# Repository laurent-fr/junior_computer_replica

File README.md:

# Junior Computer Replica

The Junior Computer is a 6502 SBC made by Elektor in 1980. It looks a lot like a KIM-1.

This is a replica PCB I made with KiCAD.

The best source of information for this computer is Elektor Magazine from 80's , but you can find a lot on this website : http://retro.hansotten.nl/6502-sbc/elektuur-junior/

This board is not a 100% accurate replica, because I have added directly on the PCB a few updates published later by Elektor :
* a fix for memory decoding needed for the expansion board
* the main decoupling capacitor C2 was on wrong side of S25 (activate display) which could reset the computer
* a simple reset circuit with a resistor and a capacitor

I also replaced the 2708 EPROM by a 2716, which avoid the need of an hard to find EPROM & EPROM programmer, and has the big benefit of reducing the required power supplies from 3 (+5,-5,+12) to only +5V.

This work is licenced under CC BY-NC-SA (Attribution-NonCommercial-ShareAlike)

## BOM

| Qty | Reference   | Value | Comment |
| --- | --- | --- | --- |
| 1	| C1 |	10p | |
| 1	| C2 |	47µ 6V tantale | |
| 2	| C3, C4 |	100n MKH
| 8	| C5...C9, C10, C11, C14 | 	1µ 16V tantale | |
| 1	| C12 |	470nF MKH | |
| 2	| D1, D3 |	1N4148 | |
| 1	| IC1 |	MC6502 | |
| 1	| IC10 |	74LS01 | |
| 1	| IC11 |	ULN2003 | |
| 1	| IC2 |	2716 | |
| 1	| IC3 |	MC6532 | probably the first part to look at ! |
| 2	| IC4 IC5 |	2114 | static RAM, search on Ebay |
| 2	| IC7 IC6 |	74LS145 | |
| 1	| IC8 |	NE556 | |
| 1	| IC9 |	74LS00 | |
| 1	| J2 |	DIN41612 32 A+C angled male| |
| 1	| J3 |	DIN41617-31 straight female | |
| 2	| R17 R19 |	2k2 | |
| 2	| R18 R20 |	68k | |
| 1 | R1 | 330K | |
| 6	| R2 R3 R4 R16 R14 R15 |	3k3 | |
| 2	| R22 R21 |	1k | |
| 1	| R23 |	820k | |
| 1	| R5 |	4k7 | |
| 1	| R6 |	330 | |
| 7	| R7 R8 R9 R10 R12 R13 R11 |	68 | |
| 21	| S1…S23 |	Digitast 12.7mm | 16 black, 4 red, 1 red with integrated LED, 2 blue, but see below |
| 1	| S24 | DPDT lever switch	| with soldering lugs |
| 1	| S25|	SPDT lever switch | with soldering lugs |
| 1	| X.Tal1 |	1Mhz | can be hard to find ! |
| 3	| Socket DIP-14	| | |
| 3	| Socket DIP-16	| | |
| 2	| Socket DIP-18	| | |
| 1	| Socket DIP-24	| | |
| 2	| Socket DIP-40	| | |
| 6 | Di1 ... Di6 | MAN4640A | 7 segment display |

IF you cannot find 2114 RAMs , you can try the small board on "board adapter" folder (warning : not tested !) which should allow to use a 6116 RAM instead and plugs into the 2114 sockets

The Digitast keys (https://www.digikey.com/catalog/en/partgroup/digitast-series/15959) are the most expensives parts of this project. You can also use square tactile switchs instead (but it's not as pretty !)

An other thing to consider is the marking : the black keys need white marking, which can be hard to do. So think of how you will do the marking before choosing the colors of the keys !

## Ordering the PCB

Use you favorite online PCB seller, and order 2 double-sided PCBs (display + computer) from the KiCad output files.

The real ones from Elektor where blue on component side and red on solder side, but if you order a blue PCB it will be close enough (and very nice).

## Building the computer

The building is pretty straightforward (look at the original documentation). Components are soldered on one side, buttons and disply on the other side.

S24 and S25 switchs needs wires from the switchs lugs to the PCB (I used cutoff of resistor leads)

To connect the display to the main board, I used long SIL connectors (15-20mm long) soldered on both side, then I bent the display to ~30°

Don't forget the two small wire jumpers on front side : one from ground to letter "D" and the other one from K6 to the center pin.

If you want to use the file sticker-juniorcomputer.svg, first install the font "Microgramma D Extended Bold" on your system.

## Programming the EPROM

I use a TL866 II plus for this, but anything that works is OK. 

Program the 2716 with the file 2716_junior_monitor_ram_05_1980.bin

## First tests

The power supply is available on both connectors, you just need 0v and +5V (1amp should be more than enough).

All the display should light up (check that the DISPLAY switch is ON). If you see some display ON, some display OFF, it could be a bad MC6532 (don't ask how I know that ...)

If nothing happens, press the reset switch to start the computer.

Typing numbers on keyboard should update the display.

You can find test programs on http://retro.hansotten.nl

## Going further

It would be great to be able to load and save data, and also to have a serial terminal for typing programs. It's exactly the purpose of the Junior Interface board ! Look into the folder "junior-interface" for more infos !

Now I'm sure you want to run BASIC on the Junior, no problem, just build the memory expansion from "junior-universal-memory" folder and you're good to go !

## Status

### Working

* junior-computer : the computer, built and tested OK
* junior-computer-display: the 7 segments display, built and tested OK
* junior-interface : the 2nd board adding various I/O to the computer, built and tested OK
* junior-internal-conn : internal bus between computer and interface, built and tested OK
* junior-internal-bus : a small PCB for linking the computer and the interface board, built and tested OK
* junior-bus : Elektor expansion bus. Not tested, built and tested OK
* junior-universal-memory : a RAM/EPROM board for the computer, built and tested OK

### Not tested

* ram-adapter : replace 2x2114 by 1x6116 RAM. Not tested

```
Any question ? --> Mastodon @LaurentFr@piaille.fr
```

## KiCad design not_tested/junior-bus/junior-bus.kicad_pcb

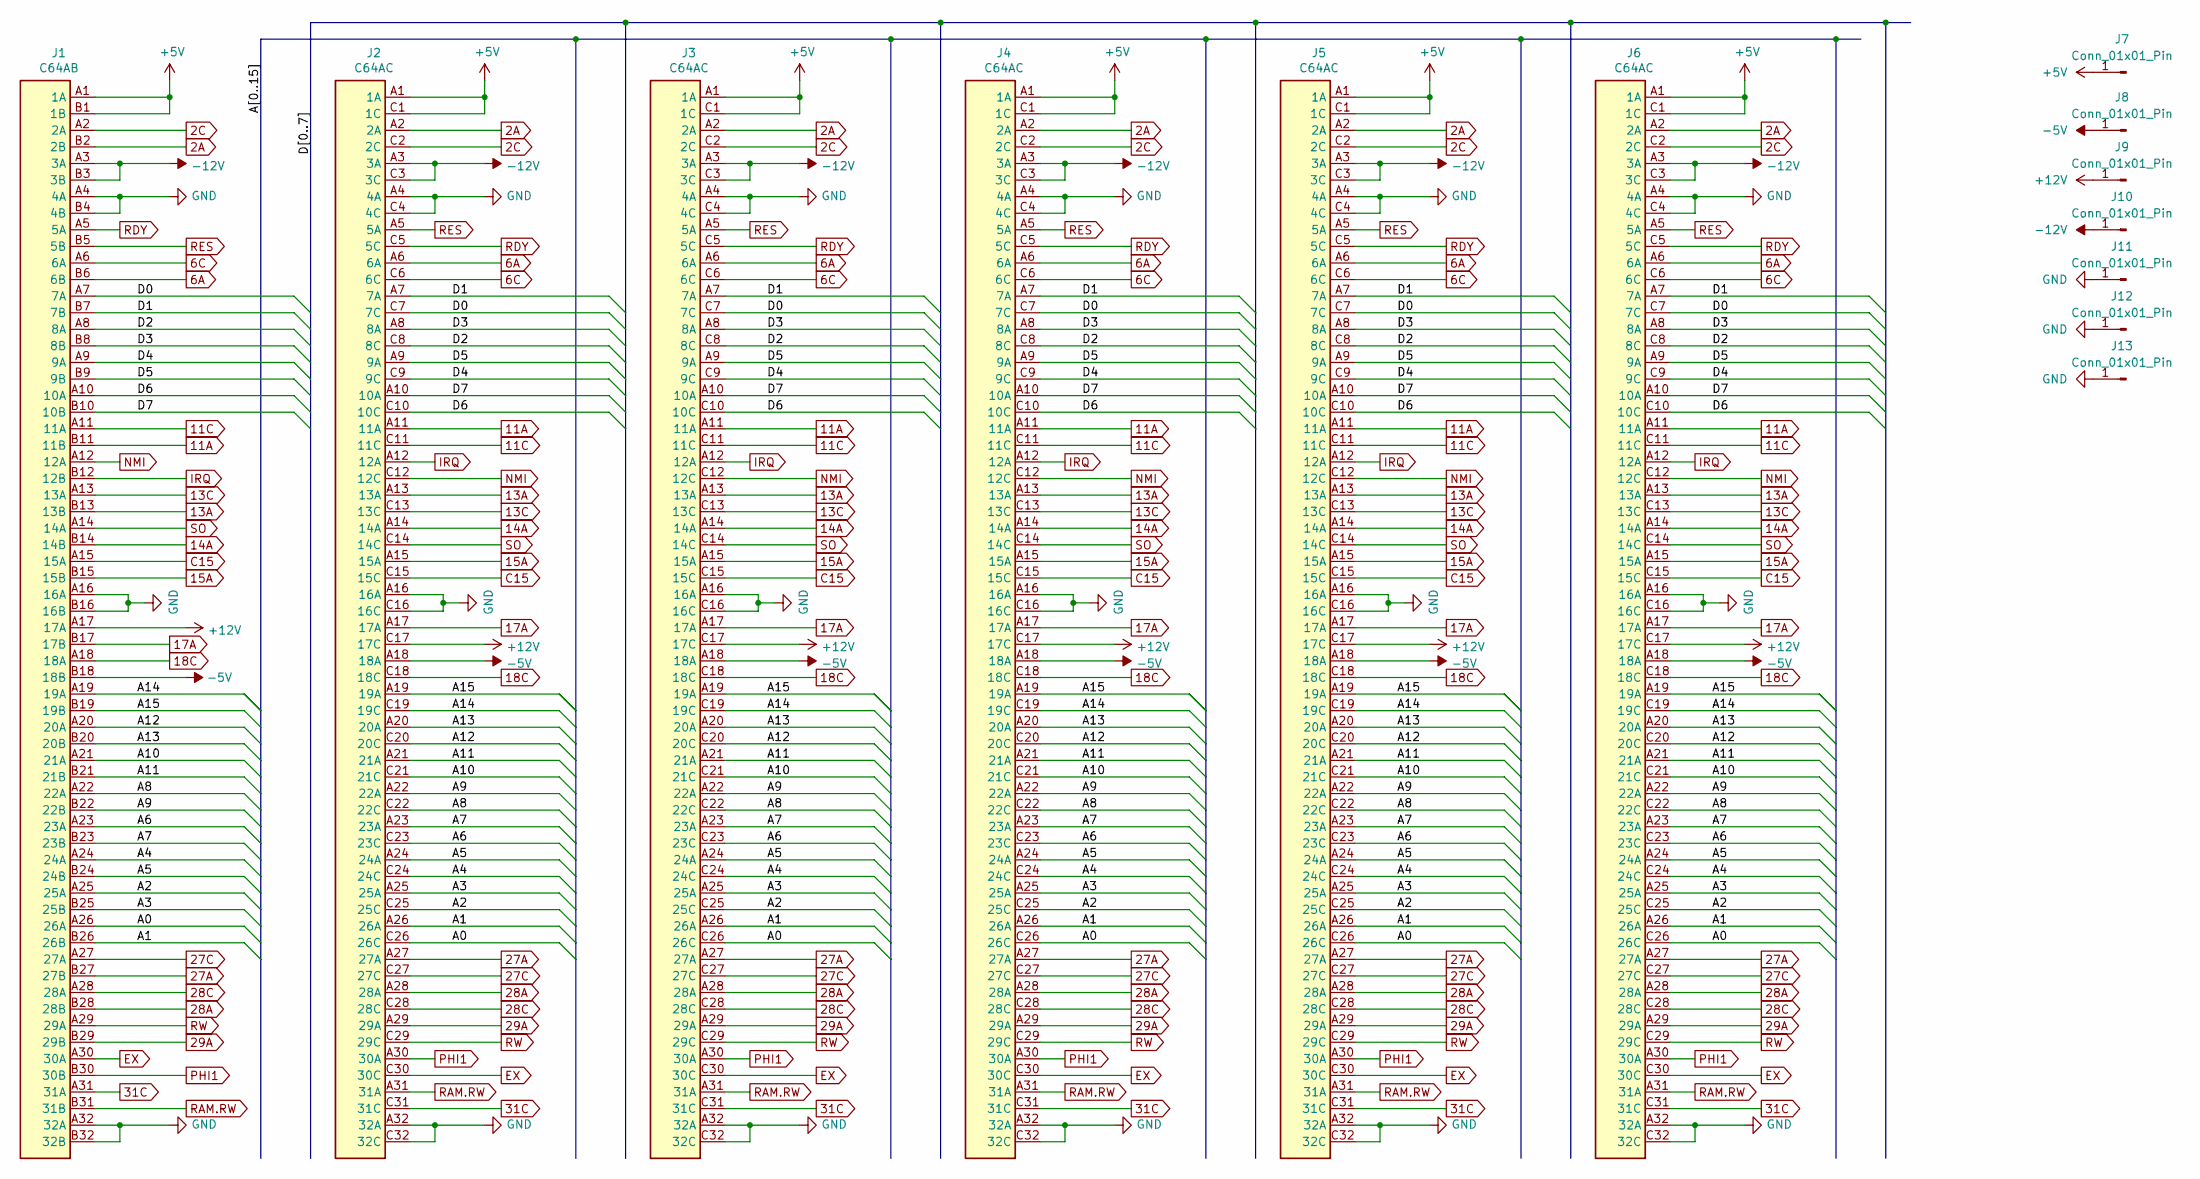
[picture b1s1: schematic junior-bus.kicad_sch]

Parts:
J1: C64AB; DIN-41612-AB-small-pads
J2, J3, J4, J5, J6: C64AC; DI41612-AC-F
J7, J8, J9, J10, J11, J12, J13: Conn_01x01_Pin; PIN

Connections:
2A: J1.B2 (2B), J2.A2 (2A), J3.A2 (2A), J4.A2 (2A), J5.A2 (2A), J6.A2 (2A)
2C: J1.A2 (2A), J2.C2 (2C), J3.C2 (2C), J4.C2 (2C), J5.C2 (2C), J6.C2 (2C)
6A: J1.B6 (6B), J2.A6 (6A), J3.A6 (6A), J4.A6 (6A), J5.A6 (6A), J6.A6 (6A)
6C: J1.A6 (6A), J2.C6 (6C), J3.C6 (6C), J4.C6 (6C), J5.C6 (6C), J6.C6 (6C)
11A: J1.B11 (11B), J2.A11 (11A), J3.A11 (11A), J4.A11 (11A), J5.A11 (11A), J6.A11 (11A)
11C: J1.A11 (11A), J2.C11 (11C), J3.C11 (11C), J4.C11 (11C), J5.C11 (11C), J6.C11 (11C)
13A: J1.B13 (13B), J2.A13 (13A), J3.A13 (13A), J4.A13 (13A), J5.A13 (13A), J6.A13 (13A)
13C: J1.A13 (13A), J2.C13 (13C), J3.C13 (13C), J4.C13 (13C), J5.C13 (13C), J6.C13 (13C)
14A: J1.B14 (14B), J2.A14 (14A), J3.A14 (14A), J4.A14 (14A), J5.A14 (14A), J6.A14 (14A)
15A: J1.B15 (15B), J2.A15 (15A), J3.A15 (15A), J4.A15 (15A), J5.A15 (15A), J6.A15 (15A)
17A: J1.B17 (17B), J2.A17 (17A), J3.A17 (17A), J4.A17 (17A), J5.A17 (17A), J6.A17 (17A)
18C: J1.A18 (18A), J2.C18 (18C), J3.C18 (18C), J4.C18 (18C), J5.C18 (18C), J6.C18 (18C)
27A: J1.B27 (27B), J2.A27 (27A), J3.A27 (27A), J4.A27 (27A), J5.A27 (27A), J6.A27 (27A)
27C: J1.A27 (27A), J2.C27 (27C), J3.C27 (27C), J4.C27 (27C), J5.C27 (27C), J6.C27 (27C)
28A: J1.B28 (28B), J2.A28 (28A), J3.A28 (28A), J4.A28 (28A), J5.A28 (28A), J6.A28 (28A)
28C: J1.A28 (28A), J2.C28 (28C), J3.C28 (28C), J4.C28 (28C), J5.C28 (28C), J6.C28 (28C)
29A: J1.B29 (29B), J2.A29 (29A), J3.A29 (29A), J4.A29 (29A), J5.A29 (29A), J6.A29 (29A)
31C: J1.A31 (31A), J2.C31 (31C), J3.C31 (31C), J4.C31 (31C), J5.C31 (31C), J6.C31 (31C)
+5V: J1.A1 (1A), J1.B1 (1B), J2.A1 (1A), J2.C1 (1C), J3.A1 (1A), J3.C1 (1C), J4.A1 (1A), J4.C1 (1C), J5.A1 (1A), J5.C1 (1C), J6.A1 (1A), J6.C1 (1C), J7.1
+12V: J1.A17 (17A), J2.C17 (17C), J3.C17 (17C), J4.C17 (17C), J5.C17 (17C), J6.C17 (17C), J9.1
-5V: J1.B18 (18B), J2.A18 (18A), J3.A18 (18A), J4.A18 (18A), J5.A18 (18A), J6.A18 (18A), J8.1
-12V: J1.A3 (3A), J1.B3 (3B), J2.A3 (3A), J2.C3 (3C), J3.A3 (3A), J3.C3 (3C), J4.A3 (3A), J4.C3 (3C), J5.A3 (3A), J5.C3 (3C), J6.A3 (3A), J6.C3 (3C), J10.1
/A0: J1.A26 (26A), J2.C26 (26C), J3.C26 (26C), J4.C26 (26C), J5.C26 (26C), J6.C26 (26C)
/A1: J1.B26 (26B), J2.A26 (26A), J3.A26 (26A), J4.A26 (26A), J5.A26 (26A), J6.A26 (26A)
/A2: J1.A25 (25A), J2.C25 (25C), J3.C25 (25C), J4.C25 (25C), J5.C25 (25C), J6.C25 (25C)
/A3: J1.B25 (25B), J2.A25 (25A), J3.A25 (25A), J4.A25 (25A), J5.A25 (25A), J6.A25 (25A)
/A4: J1.A24 (24A), J2.C24 (24C), J3.C24 (24C), J4.C24 (24C), J5.C24 (24C), J6.C24 (24C)
/A5: J1.B24 (24B), J2.A24 (24A), J3.A24 (24A), J4.A24 (24A), J5.A24 (24A), J6.A24 (24A)
/A6: J1.A23 (23A), J2.C23 (23C), J3.C23 (23C), J4.C23 (23C), J5.C23 (23C), J6.C23 (23C)
/A7: J1.B23 (23B), J2.A23 (23A), J3.A23 (23A), J4.A23 (23A), J5.A23 (23A), J6.A23 (23A)
/A8: J1.A22 (22A), J2.C22 (22C), J3.C22 (22C), J4.C22 (22C), J5.C22 (22C), J6.C22 (22C)
/A9: J1.B22 (22B), J2.A22 (22A), J3.A22 (22A), J4.A22 (22A), J5.A22 (22A), J6.A22 (22A)
/A10: J1.A21 (21A), J2.C21 (21C), J3.C21 (21C), J4.C21 (21C), J5.C21 (21C), J6.C21 (21C)
/A11: J1.B21 (21B), J2.A21 (21A), J3.A21 (21A), J4.A21 (21A), J5.A21 (21A), J6.A21 (21A)
/A12: J1.A20 (20A), J2.C20 (20C), J3.C20 (20C), J4.C20 (20C), J5.C20 (20C), J6.C20 (20C)
/A13: J1.B20 (20B), J2.A20 (20A), J3.A20 (20A), J4.A20 (20A), J5.A20 (20A), J6.A20 (20A)
/A14: J1.A19 (19A), J2.C19 (19C), J3.C19 (19C), J4.C19 (19C), J5.C19 (19C), J6.C19 (19C)
/A15: J1.B19 (19B), J2.A19 (19A), J3.A19 (19A), J4.A19 (19A), J5.A19 (19A), J6.A19 (19A)
/D0: J1.A7 (7A), J2.C7 (7C), J3.C7 (7C), J4.C7 (7C), J5.C7 (7C), J6.C7 (7C)
/D1: J1.B7 (7B), J2.A7 (7A), J3.A7 (7A), J4.A7 (7A), J5.A7 (7A), J6.A7 (7A)
/D2: J1.A8 (8A), J2.C8 (8C), J3.C8 (8C), J4.C8 (8C), J5.C8 (8C), J6.C8 (8C)
/D3: J1.B8 (8B), J2.A8 (8A), J3.A8 (8A), J4.A8 (8A), J5.A8 (8A), J6.A8 (8A)
/D4: J1.A9 (9A), J2.C9 (9C), J3.C9 (9C), J4.C9 (9C), J5.C9 (9C), J6.C9 (9C)
/D5: J1.B9 (9B), J2.A9 (9A), J3.A9 (9A), J4.A9 (9A), J5.A9 (9A), J6.A9 (9A)
/D6: J1.A10 (10A), J2.C10 (10C), J3.C10 (10C), J4.C10 (10C), J5.C10 (10C), J6.C10 (10C)
/D7: J1.B10 (10B), J2.A10 (10A), J3.A10 (10A), J4.A10 (10A), J5.A10 (10A), J6.A10 (10A)
C15: J1.A15 (15A), J2.C15 (15C), J3.C15 (15C), J4.C15 (15C), J5.C15 (15C), J6.C15 (15C)
EX: J1.A30 (30A), J2.C30 (30C), J3.C30 (30C), J4.C30 (30C), J5.C30 (30C), J6.C30 (30C)
GND: J1.A4 (4A), J1.A16 (16A), J1.A32 (32A), J1.B4 (4B), J1.B16 (16B), J1.B32 (32B), J2.A4 (4A), J2.A16 (16A), J2.A32 (32A), J2.C4 (4C), J2.C16 (16C), J2.C32 (32C), J3.A4 (4A), J3.A16 (16A), J3.A32 (32A), J3.C4 (4C), J3.C16 (16C), J3.C32 (32C), J4.A4 (4A), J4.A16 (16A), J4.A32 (32A), J4.C4 (4C), J4.C16 (16C), J4.C32 (32C), J5.A4 (4A), J5.A16 (16A), J5.A32 (32A), J5.C4 (4C), J5.C16 (16C), J5.C32 (32C), J6.A4 (4A), J6.A16 (16A), J6.A32 (32A), J6.C4 (4C), J6.C16 (16C), J6.C32 (32C), J11.1, J12.1, J13.1
IRQ: J1.B12 (12B), J2.A12 (12A), J3.A12 (12A), J4.A12 (12A), J5.A12 (12A), J6.A12 (12A)
NMI: J1.A12 (12A), J2.C12 (12C), J3.C12 (12C), J4.C12 (12C), J5.C12 (12C), J6.C12 (12C)
PHI1: J1.B30 (30B), J2.A30 (30A), J3.A30 (30A), J4.A30 (30A), J5.A30 (30A), J6.A30 (30A)
RAM.RW: J1.B31 (31B), J2.A31 (31A), J3.A31 (31A), J4.A31 (31A), J5.A31 (31A), J6.A31 (31A)
RDY: J1.A5 (5A), J2.C5 (5C), J3.C5 (5C), J4.C5 (5C), J5.C5 (5C), J6.C5 (5C)
RES: J1.B5 (5B), J2.A5 (5A), J3.A5 (5A), J4.A5 (5A), J5.A5 (5A), J6.A5 (5A)
RW: J1.A29 (29A), J2.C29 (29C), J3.C29 (29C), J4.C29 (29C), J5.C29 (29C), J6.C29 (29C)
SO: J1.A14 (14A), J2.C14 (14C), J3.C14 (14C), J4.C14 (14C), J5.C14 (14C), J6.C14 (14C)

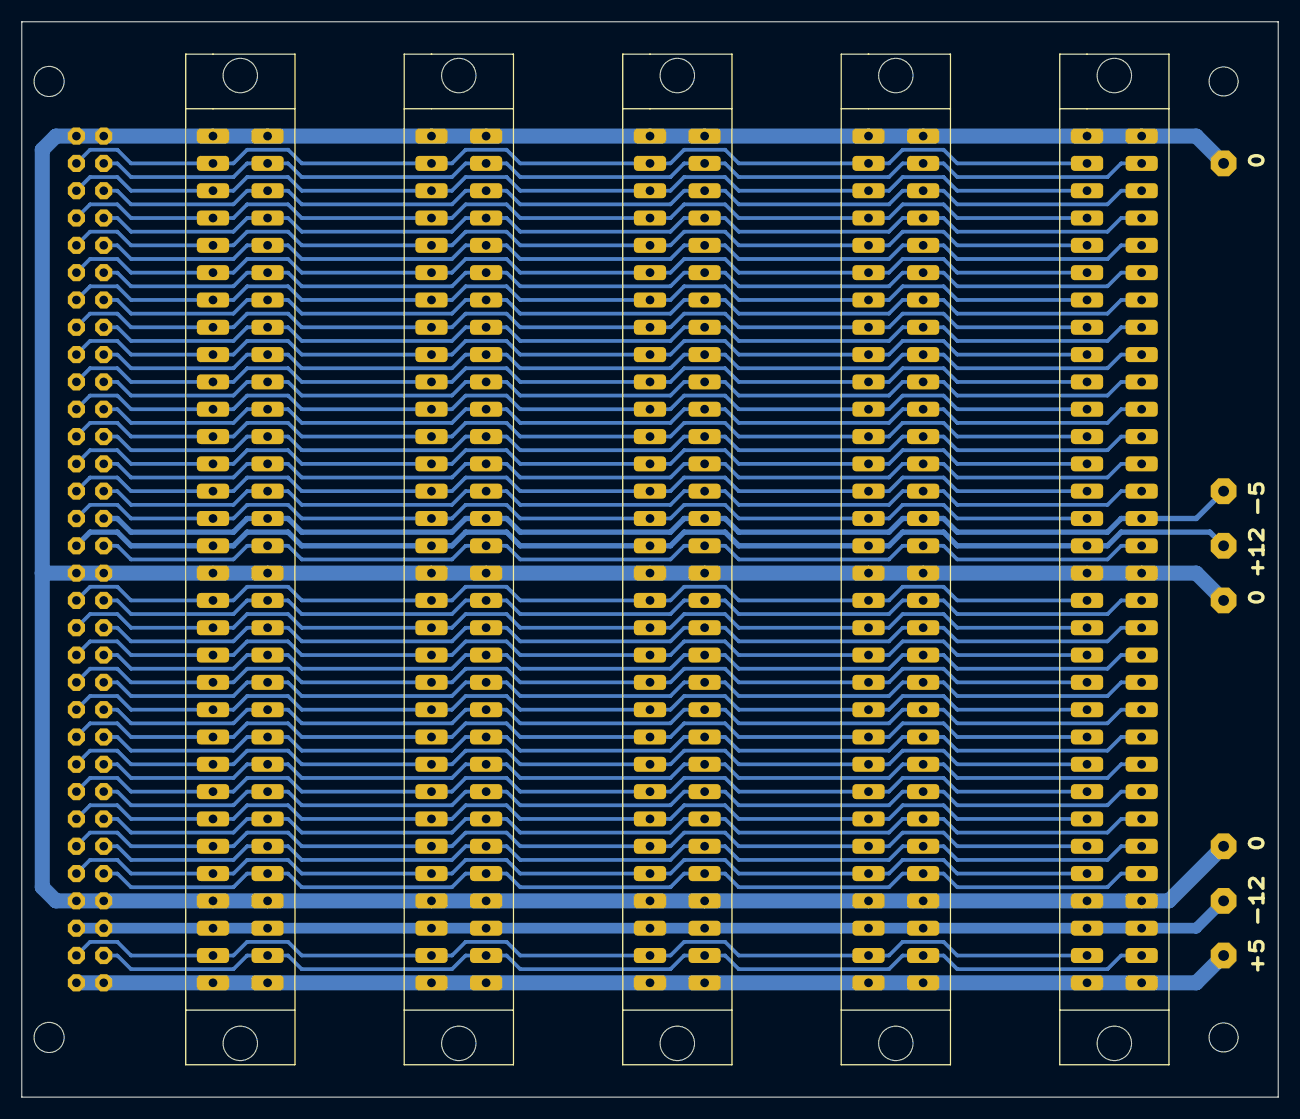
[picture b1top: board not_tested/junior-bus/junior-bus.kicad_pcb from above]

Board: 2 copper layers, 116.8 x 100.0 mm, 15 parts (1 on the bottom side), 57 nets.

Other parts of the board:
REF1, REF2: MountingHole_2.7mm_M2.5_ISO14580

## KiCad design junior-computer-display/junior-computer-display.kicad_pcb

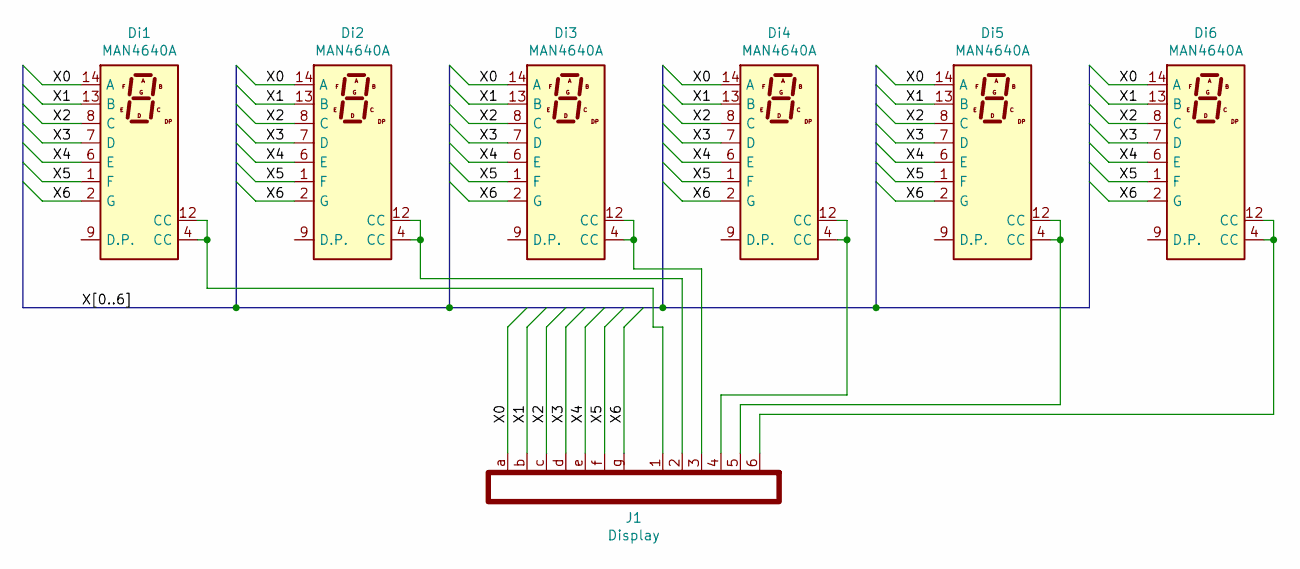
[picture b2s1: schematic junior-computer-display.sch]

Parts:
Di1, Di2, Di3, Di4, Di5, Di6: MAN4640A; 7SEGMENT
J1: Display; Conn-Display-Top

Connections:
/X0: Di1.14 (A), Di2.14 (A), Di3.14 (A), Di4.14 (A), Di5.14 (A), Di6.14 (A), J1.a
/X1: Di1.13 (B), Di2.13 (B), Di3.13 (B), Di4.13 (B), Di5.13 (B), Di6.13 (B), J1.b
/X2: Di1.8 (C), Di2.8 (C), Di3.8 (C), Di4.8 (C), Di5.8 (C), Di6.8 (C), J1.c
/X3: Di1.7 (D), Di2.7 (D), Di3.7 (D), Di4.7 (D), Di5.7 (D), Di6.7 (D), J1.d
/X4: Di1.6 (E), Di2.6 (E), Di3.6 (E), Di4.6 (E), Di5.6 (E), Di6.6 (E), J1.e
/X5: Di1.1 (F), Di2.1 (F), Di3.1 (F), Di4.1 (F), Di5.1 (F), Di6.1 (F), J1.f
/X6: Di1.2 (G), Di2.2 (G), Di3.2 (G), Di4.2 (G), Di5.2 (G), Di6.2 (G), J1.g
unnamed: Di1.4 (CC), Di1.12 (CC), J1.1
unnamed: Di2.4 (CC), Di2.12 (CC), J1.2
unnamed: Di3.4 (CC), Di3.12 (CC), J1.3
unnamed: Di4.4 (CC), Di4.12 (CC), J1.4
unnamed: Di5.4 (CC), Di5.12 (CC), J1.5
unnamed: Di6.4 (CC), Di6.12 (CC), J1.6

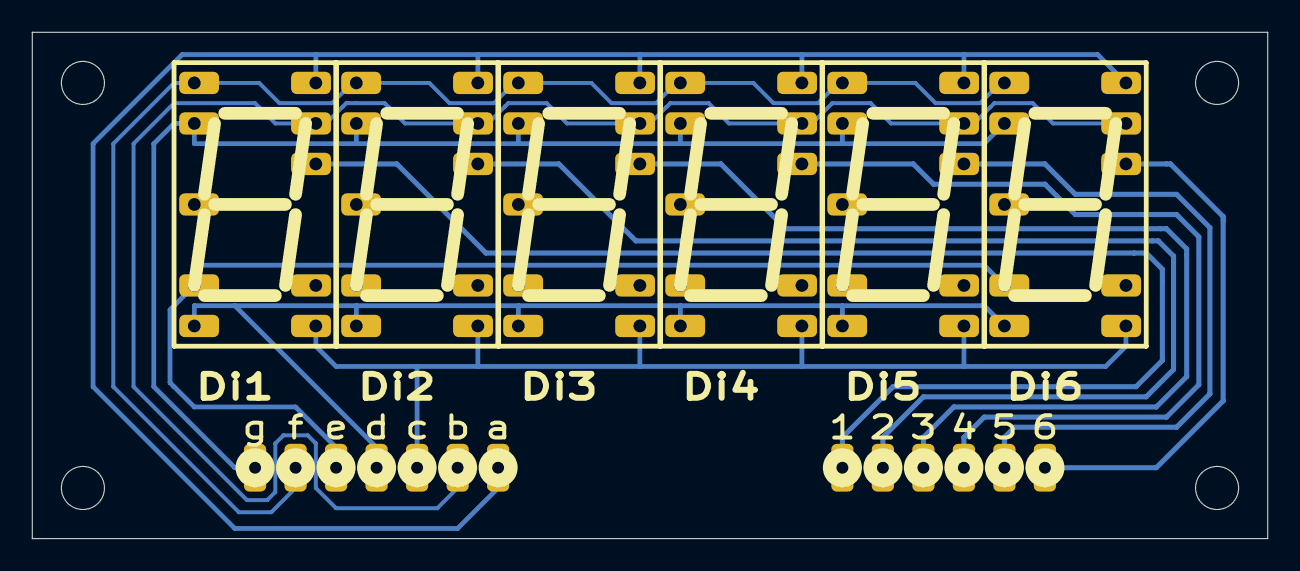
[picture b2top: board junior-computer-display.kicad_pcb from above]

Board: 2 copper layers, 77.5 x 31.8 mm, 7 parts (0 on the bottom side), 13 nets.

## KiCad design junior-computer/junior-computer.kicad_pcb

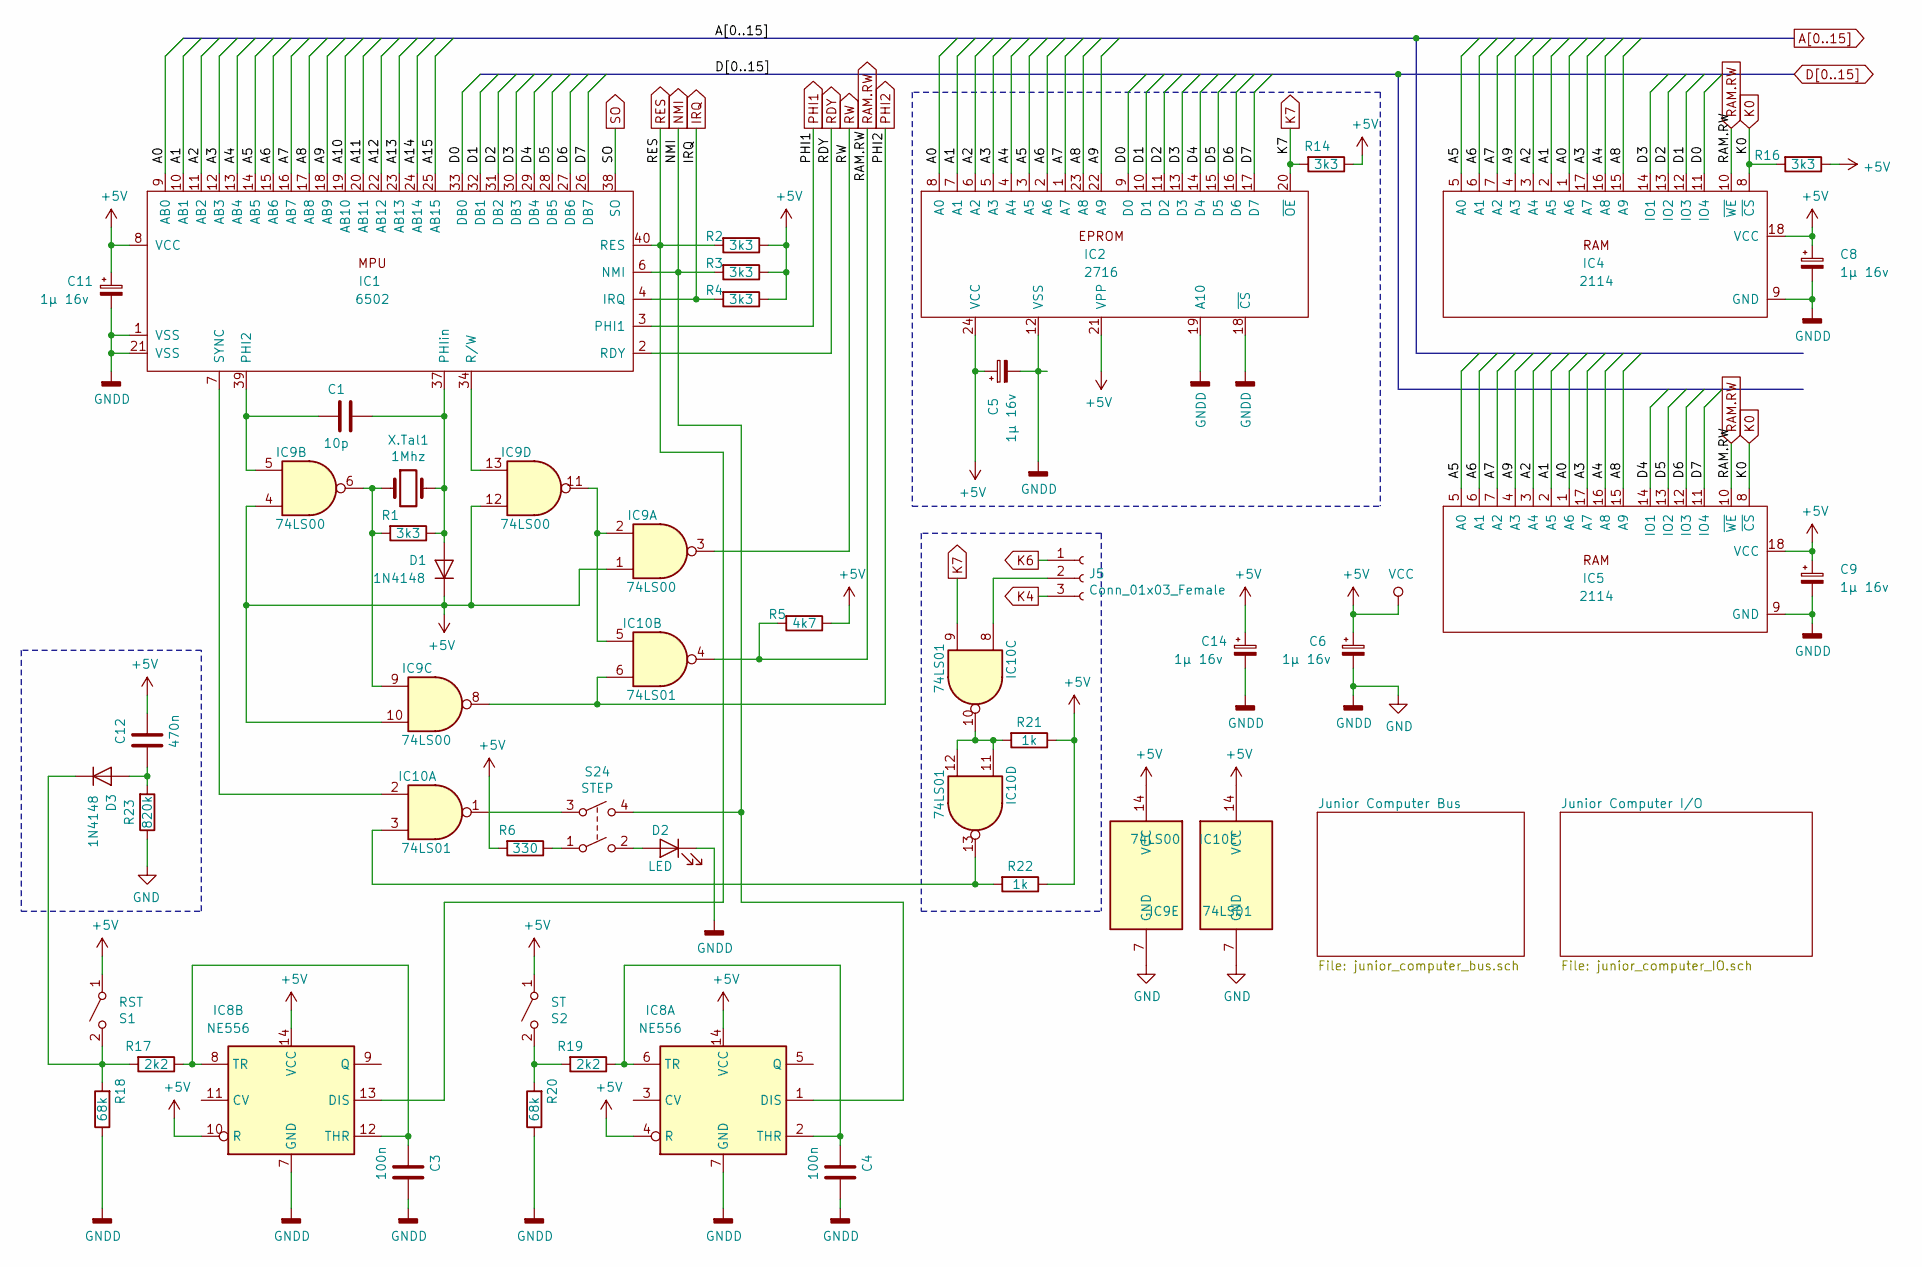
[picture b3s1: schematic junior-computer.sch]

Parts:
C1: 10p; CAP-2
C3, C4: 100n; CAP-3
C5: 1µ 16v; CAP-POL-2
C6, C9, C11, C14: 1µ 16v; CAP-POL-3
C8: 1µ 16v; CAP-POL-1.5
C12: 470n; CAP-2-HEX
D1, D3: 1N4148; Diod-4
D2: LED; Digitast-LED
IC1: 6502; DIL-40
IC2: 2716; DIL-24
IC4, IC5: 2114; DIL-18
IC8: NE556; DIL-14
IC9: 74LS00; DIL-14
IC10: 74LS01; DIL-14
J5: Conn_01x03_Female; K4-K6
R1, R2, R3, R4, R14, R16: 3k3; Res-5
R5: 4k7; Res-5
R6: 330; Res-5
R17, R19: 2k2; Res-5
R18, R20: 68k; Res-5
R21, R22: 1k; Res-5
R23: 820k; Res-5
S1: RST; Digitast
S2: ST; Digitast
S24: STEP; SW-2T
X.Tal1: 1Mhz; Quartz

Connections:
+5V: C5.1, C6.1, C8.1, C9.1, C11.1, C12.2, C14.1, D1.1 (K), IC1.8 (VCC), IC2.21 (VPP), IC2.24 (VCC), IC4.18 (VCC), IC5.18 (VCC), IC8.4 (R), IC8.10 (R), IC8.14 (VCC), IC9.1, IC9.4, IC9.10, IC9.12, IC9.14 (VCC), IC10.14 (VCC), R2.1, R3.1, R4.1, R5.1, R6.2, R14.1, R16.1, R21.1, R22.1, S1.1 (A), S2.1 (A); also elsewhere on the board
A0: IC1.9 (AB0), IC2.8 (A0), IC4.1 (A6), IC5.1 (A6); also elsewhere on the board
A1: IC1.10 (AB1), IC2.7 (A1), IC4.2 (A5), IC5.2 (A5); also elsewhere on the board
A2: IC1.11 (AB2), IC2.6 (A2), IC4.3 (A4), IC5.3 (A4); also elsewhere on the board
A3: IC1.12 (AB3), IC2.5 (A3), IC4.17 (A7), IC5.17 (A7); also elsewhere on the board
A4: IC1.13 (AB4), IC2.4 (A4), IC4.16 (A8), IC5.16 (A8); also elsewhere on the board
A5: IC1.14 (AB5), IC2.3 (A5), IC4.5 (A0), IC5.5 (A0); also elsewhere on the board
A6: IC1.15 (AB6), IC2.2 (A6), IC4.6 (A1), IC5.6 (A1); also elsewhere on the board
A7: IC1.16 (AB7), IC2.1 (A7), IC4.7 (A2), IC5.7 (A2); also elsewhere on the board
A8: IC1.17 (AB8), IC2.23 (A8), IC4.15 (A9), IC5.15 (A9); also elsewhere on the board
A9: IC1.18 (AB9), IC2.22 (A9), IC4.4 (A3), IC5.4 (A3); also elsewhere on the board
A10: IC1.19 (AB10); also elsewhere on the board
A11: IC1.20 (AB11); also elsewhere on the board
A12: IC1.22 (AB12); also elsewhere on the board
A13: IC1.23 (AB13); also elsewhere on the board
A14: IC1.24 (AB14); also elsewhere on the board
A15: IC1.25 (AB15); also elsewhere on the board
D0: IC1.33 (DB0), IC2.9 (D0), IC4.11 (IO4); also elsewhere on the board
D1: IC1.32 (DB1), IC2.10 (D1), IC4.12 (IO3); also elsewhere on the board
D2: IC1.31 (DB2), IC2.11 (D2), IC4.13 (IO2); also elsewhere on the board
D3: IC1.30 (DB3), IC2.13 (D3), IC4.14 (IO1); also elsewhere on the board
D4: IC1.29 (DB4), IC2.14 (D4), IC5.14 (IO1); also elsewhere on the board
D5: IC1.28 (DB5), IC2.15 (D5), IC5.13 (IO2); also elsewhere on the board
D6: IC1.27 (DB6), IC2.16 (D6), IC5.12 (IO3); also elsewhere on the board
D7: IC1.26 (DB7), IC2.17 (D7), IC5.11 (IO4); also elsewhere on the board
GND: C3.1, C4.1, C5.2, C6.2, C8.2, C9.2, C11.2, C14.2, D2.1 (K), IC1.1 (VSS), IC1.21 (VSS), IC2.12 (VSS), IC2.18 (~CS~), IC2.19 (A10), IC4.9 (GND), IC5.9 (GND), IC8.7 (GND), IC9.7 (GND), IC10.7 (GND), R18.1, R20.1, R23.1; also elsewhere on the board
IRQ: IC1.4 (IRQ), R4.2; also elsewhere on the board
K0: IC4.8 (~CS~), IC5.8 (~CS~), R16.2; also elsewhere on the board
K4: J5.3; also elsewhere on the board
K6: J5.1; also elsewhere on the board
K7: IC2.20 (~OE~), IC10.9, R14.2; also elsewhere on the board
NMI: IC1.6 (NMI), IC8.1 (DIS), R3.2, S24.4; also elsewhere on the board
unnamed 39: C1.1, D1.2 (A), IC1.37 (PHIin), R1.1, X.Tal1.2; also elsewhere on the board
unnamed: C1.2, IC1.39 (PHI2), IC9.5
unnamed: C3.2, IC8.8 (TR), IC8.12 (THR), R17.1
unnamed: C4.2, IC8.2 (THR), IC8.6 (TR), R19.1
unnamed: C12.1, D3.2 (A), R23.2
unnamed: D2.2 (A), S24.2
unnamed: D3.1 (K), R17.2, R18.2, S1.2 (B)
unnamed: IC1.7 (SYNC), IC10.2
unnamed: IC1.34 (R/W), IC9.13
unnamed 65: IC9.6, IC9.9, R1.2, X.Tal1.1; also elsewhere on the board
unnamed: IC10.1, S24.3
unnamed: IC9.2, IC9.11, IC10.5
unnamed: IC10.8, J5.2
unnamed: IC10.10, IC10.11, IC10.12, R21.2
unnamed: IC10.3, IC10.13, R22.2
unnamed: R6.1, S24.1
unnamed: R19.2, R20.2, S2.2 (B)
PHI1: IC1.3 (PHI1); also elsewhere on the board
PHI2: IC9.8, IC10.6; also elsewhere on the board
RAM.RW: IC4.10 (~WE~), IC5.10 (~WE~), IC10.4, R5.2; also elsewhere on the board
RDY: IC1.2 (RDY); also elsewhere on the board
RES: IC1.40 (RES), IC8.13 (DIS), R2.2; also elsewhere on the board
RW: IC9.3; also elsewhere on the board
SO: IC1.38 (SO); also elsewhere on the board

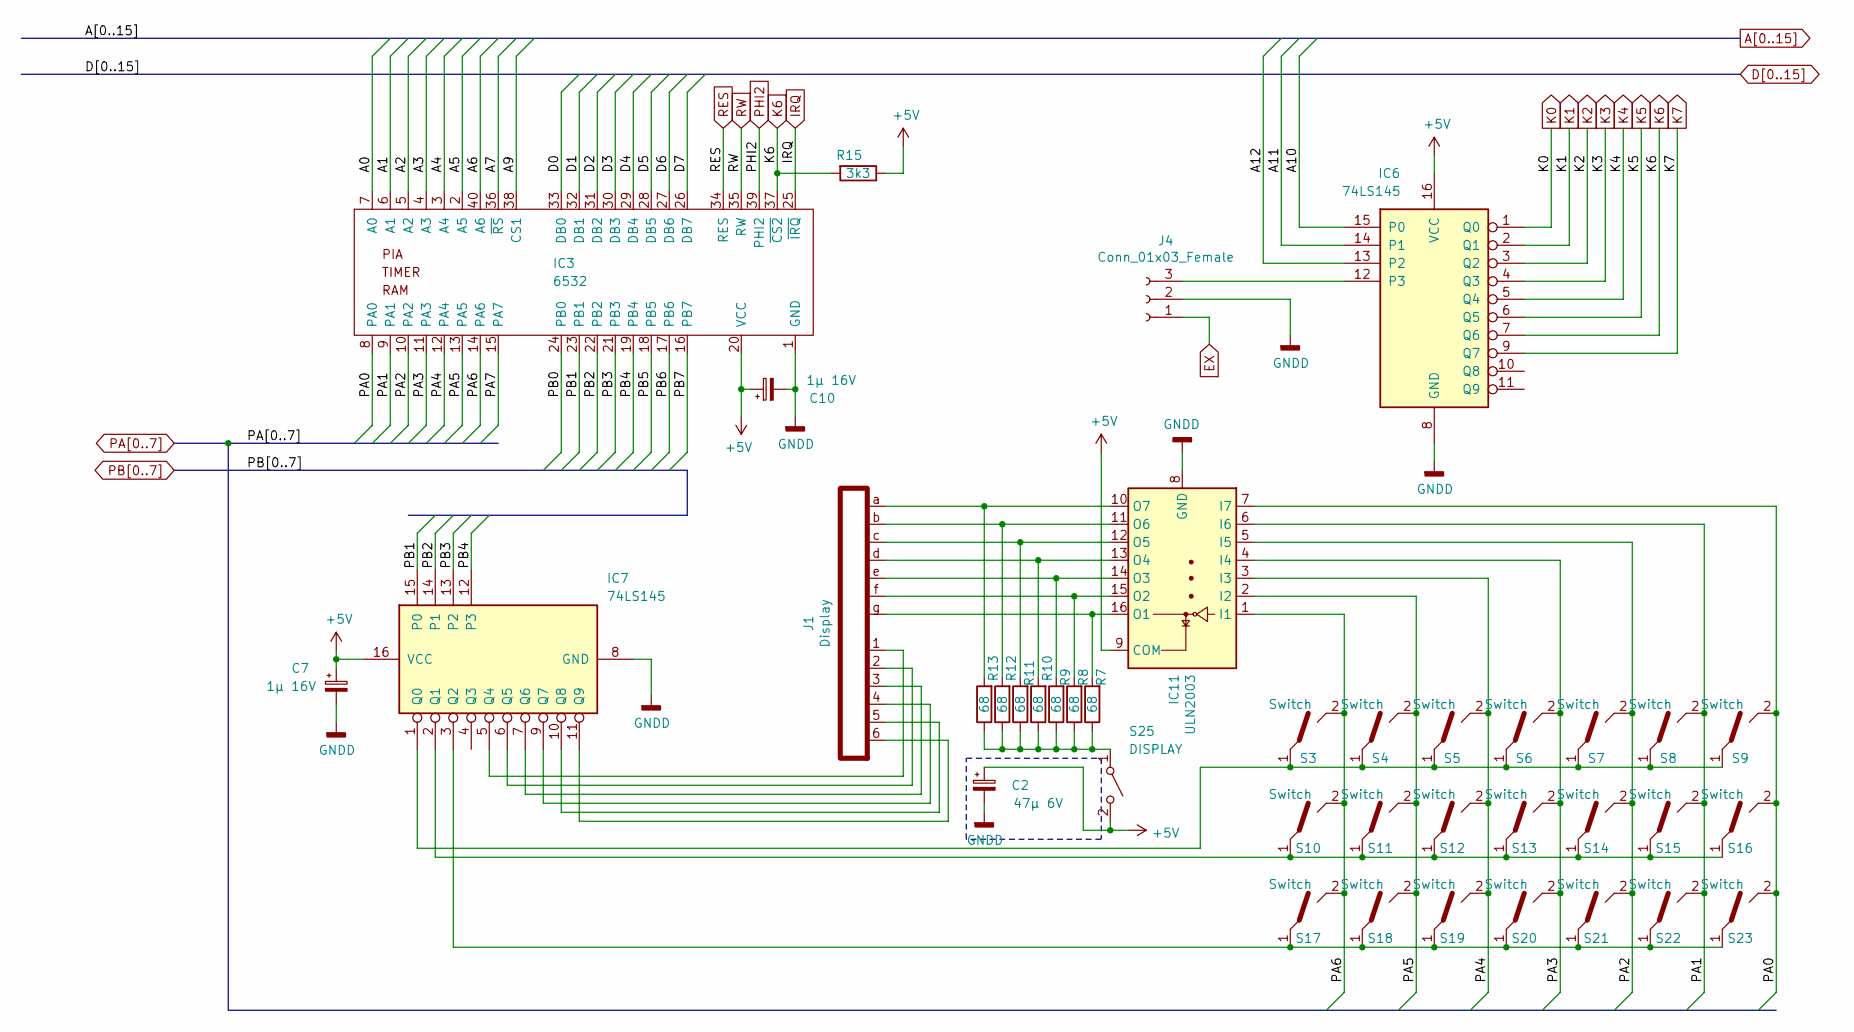
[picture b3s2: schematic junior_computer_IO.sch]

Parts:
C2: 47µ 6V; CAP-POL-5
C7: 1µ 16V; CAP-POL-3
C10: 1µ 16V; CAP-POL-2
IC3: 6532; DIL-40
IC6, IC7: 74LS145; DIL-16
IC11: ULN2003; DIL-16
J1: Display; Conn-Display-Bottom
J4: Conn_01x03_Female; Jumper-D-EX
R7, R8, R9, R10, R11, R12, R13: 68; Res-5
R15: 3k3; Res-5
S3, S4, S5, S6, S7, S8, S9, S10, S11, S12, S13, S14, S15, S16, S17, S18, S19, S20, S21, S22, S23: Switch; Digitast
S25: DISPLAY; SW-1T

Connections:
+5V: C2.1, C7.1, C10.1, IC3.20 (VCC), IC6.16 (VCC), IC7.16 (VCC), IC11.9 (COM), R15.1, S25.2 (B); also elsewhere on the board
A0: IC3.7 (A0); also elsewhere on the board
A1: IC3.6 (A1); also elsewhere on the board
A2: IC3.5 (A2); also elsewhere on the board
A3: IC3.4 (A3); also elsewhere on the board
A4: IC3.3 (A4); also elsewhere on the board
A5: IC3.2 (A5); also elsewhere on the board
A6: IC3.40 (A6); also elsewhere on the board
A7: IC3.36 (~RS~); also elsewhere on the board
A9: IC3.38 (CS1); also elsewhere on the board
A10: IC6.15 (P0); also elsewhere on the board
A11: IC6.14 (P1); also elsewhere on the board
A12: IC6.13 (P2); also elsewhere on the board
D0: IC3.33 (DB0); also elsewhere on the board
D1: IC3.32 (DB1); also elsewhere on the board
D2: IC3.31 (DB2); also elsewhere on the board
D3: IC3.30 (DB3); also elsewhere on the board
D4: IC3.29 (DB4); also elsewhere on the board
D5: IC3.28 (DB5); also elsewhere on the board
D6: IC3.27 (DB6); also elsewhere on the board
D7: IC3.26 (DB7); also elsewhere on the board
EX: J4.1; also elsewhere on the board
GND: C2.2, C7.2, C10.2, IC3.1 (GND), IC6.8 (GND), IC7.8 (GND), IC11.8 (GND), J4.2; also elsewhere on the board
IRQ: IC3.25 (~IRQ~); also elsewhere on the board
K0: IC6.1 (Q0); also elsewhere on the board
K1: IC6.2 (Q1); also elsewhere on the board
K2: IC6.3 (Q2); also elsewhere on the board
K3: IC6.4 (Q3); also elsewhere on the board
K4: IC6.5 (Q4); also elsewhere on the board
K5: IC6.6 (Q5); also elsewhere on the board
K6: IC3.37 (~CS2~), IC6.7 (Q6), R15.2; also elsewhere on the board
K7: IC6.9 (Q7); also elsewhere on the board
unnamed: IC6.12 (P3), J4.3
unnamed: IC7.1 (Q0), S3.1, S4.1, S5.1, S6.1, S7.1, S8.1, S9.1
unnamed: IC7.2 (Q1), S10.1, S11.1, S12.1, S13.1, S14.1, S15.1, S16.1
unnamed: IC7.3 (Q2), S17.1, S18.1, S19.1, S20.1, S21.1, S22.1, S23.1
unnamed: IC7.5 (Q4), J1.1
unnamed: IC7.6 (Q5), J1.2
unnamed: IC7.7 (Q6), J1.3
unnamed: IC7.9 (Q7), J1.4
unnamed: IC7.10 (Q8), J1.5
unnamed: IC7.11 (Q9), J1.6
unnamed: IC11.10 (O7), J1.a, R13.2
unnamed: IC11.11 (O6), J1.b, R12.2
unnamed: IC11.12 (O5), J1.c, R11.2
unnamed: IC11.13 (O4), J1.d, R10.2
unnamed: IC11.14 (O3), J1.e, R9.2
unnamed: IC11.15 (O2), J1.f, R8.2
unnamed: IC11.16 (O1), J1.g, R7.2
unnamed: R7.1, R8.1, R9.1, R10.1, R11.1, R12.1, R13.1, S25.1 (A)
PA0: IC3.8 (PA0), IC11.7 (I7), S9.2, S16.2, S23.2; also elsewhere on the board
PA1: IC3.9 (PA1), IC11.6 (I6), S8.2, S15.2, S22.2; also elsewhere on the board
PA2: IC3.10 (PA2), IC11.5 (I5), S7.2, S14.2, S21.2; also elsewhere on the board
PA3: IC3.11 (PA3), IC11.4 (I4), S6.2, S13.2, S20.2; also elsewhere on the board
PA4: IC3.12 (PA4), IC11.3 (I3), S5.2, S12.2, S19.2; also elsewhere on the board
PA5: IC3.13 (PA5), IC11.2 (I2), S4.2, S11.2, S18.2; also elsewhere on the board
PA6: IC3.14 (PA6), IC11.1 (I1), S3.2, S10.2, S17.2; also elsewhere on the board
PA7: IC3.15 (PA7); also elsewhere on the board
PB0: IC3.24 (PB0); also elsewhere on the board
PB1: IC3.23 (PB1), IC7.15 (P0); also elsewhere on the board
PB2: IC3.22 (PB2), IC7.14 (P1); also elsewhere on the board
PB3: IC3.21 (PB3), IC7.13 (P2); also elsewhere on the board
PB4: IC3.19 (PB4), IC7.12 (P3); also elsewhere on the board
PB5: IC3.18 (PB5); also elsewhere on the board
PB6: IC3.17 (PB6); also elsewhere on the board
PB7: IC3.16 (PB7); also elsewhere on the board
PHI2: IC3.39 (PHI2); also elsewhere on the board
RES: IC3.34 (RES); also elsewhere on the board
RW: IC3.35 (RW); also elsewhere on the board
